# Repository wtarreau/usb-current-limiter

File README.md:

# Fixed or adjustable USB current limiter

When designing USB-powered devices, it's very important to be able to limit the current in order to protect the new device, as well as the USB port (typically the computer's). A simple serial resistor doesn't work as it causes a voltage drop that the device might not necessarily be able to cope with.

## Simple solution

It's easy to make a current limiter using a good old LM317, there are hundreds of such designs everywhere on the net. The main issue is that it drops at least 3 Volts, so you have to bring a 8V power supply on your USB connections, which can be even more dangerous for the board and the PC.

Instead, this project makes use of [Micrel's (now Microchip) MIC2544](http://ww1.microchip.com/downloads/en/DeviceDoc/mic2544.pdf). It's a high-side current limiter switch. It's perfect for hobbyists as it comes in an easily solderable SOP8 package and only requires one external resistor to set the current limit and an optional LED to report the overcurrent condition. The SOP8 package is large enough to let the two USB D+/D- lanes pass under, and allows to make an easy single-sided PCB. It can limit from something like 100mA to 1.5A or so.

The device photographed below was made the evening I found it in my mailbox. It was picked a bit too early from the acid bath, which explains why the copper tracks are not clean, but they are OK. At the last moment I preferred to solder a tiny 1k potentiometer that I already had instead of a fixed divider. The current limit precision is not very precise but we're speaking about saving chips from frying, so even 10% accuracy would be awesome.

Below it is connected to a freshly assembled [Breadbee board](https://github.com/breadbee/breadbee) board which it managed to protect:

## Schematic

The schematic was made with Eagle 7.7 and is provided in the directory.

## Board

The board is single-sided and doens't need any hole. A few versions of the rendered PCB are provided in the [output directory](output/), at 300 and 600 dpi and as a PDF. It's also provided as an Eagle `.brd` file.

## Bill of materials

Name | Value
-----|-------
 IC1 | MIC2544
 R1  | Rset = 230/current. e.g. 1k = 230mA
 R2  | 330-510 ohm (optional, for the overcurrent LED)
 R3  | optional, extra inrush current (230/Iamp)
 C1  | optional, inrush current duration. E.g. 1 µF
 D1  | optional, overcurrent red LED
 J1  | USB-A male connector (or PCB traces)
 X1  | USB-A female connector

## Other options

Other options include [ANALOGIC TECH's AAT4610](http://www1.futureelectronics.com/doc/ANALOGICTECH%20-%20AATI/AAT4610IGV-T1.pdf), which comes in a much smaller SOT23-5 package and doesn't have a LED output, or making your own solution using a shunt resistor and a rail-to-rail op amp such as [Microchip's MCP6001](https://ww1.microchip.com/downloads/en/DeviceDoc/MCP6001-1R-1U-2-4-1-MHz-Low-Power-Op-Amp-DS20001733L.pdf), coupled with a high-side, low-voltage, P-channel MOSFET. In the end, the MIC2544 already has everything included and is quite cheap so it seems to remain the best option for hobbyists.

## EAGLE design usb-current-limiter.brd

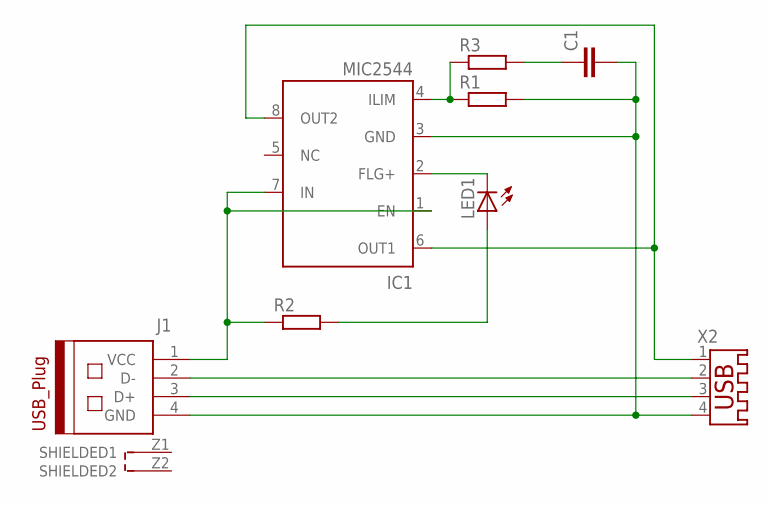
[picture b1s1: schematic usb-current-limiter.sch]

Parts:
C1: C-EUC0805K; C0805K
IC1: MIC2544; SO-08
J1: 629004113921
LED1: LEDCHIPLED_0805; CHIPLED_0805
R1, R2, R3: R-EU_M0805; M0805
X2: USB-A003

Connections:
unnamed: IC1.1 (EN), IC1.7 (IN), J1.1 (VCC), R2.1
unnamed: J1.2 (D-), X2.2
unnamed: J1.3 (D+), X2.3
unnamed: C1.2, IC1.3 (GND), J1.4 (GND), R1.2, X2.4
unnamed: IC1.6 (OUT1), IC1.8 (OUT2), X2.1
unnamed: IC1.4 (ILIM), R1.1, R3.1
unnamed: IC1.2 (FLG+), LED1.C
unnamed: LED1.A, R2.2
unnamed: C1.1, R3.2

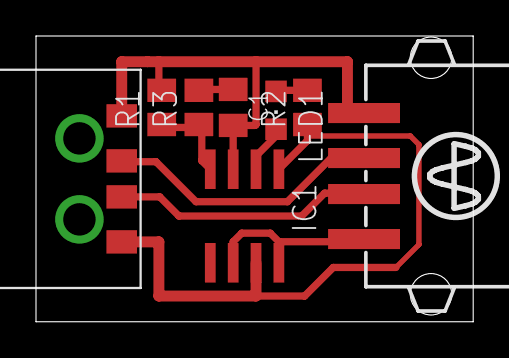
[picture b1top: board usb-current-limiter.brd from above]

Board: 2 copper layers, 24.3 x 15.9 mm, 8 parts (0 on the bottom side), 9 nets.

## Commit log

2020-09-07 First working version
    This one is easy to solder, uses 0805 resistors and an SOP8 package
    for the MIC2544. It uses no PTH components.
2020-09-07 output: provide PNG and PDF outputs
    This is the top side (both copper and components) in PDF and in PNG at
    300 and 600 DPI respectively, ready to be printed, and the schematic.
2020-09-07 photos: add a few photos
    People love photos!
2020-09-07 add a README

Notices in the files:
parts and their libraries:
Wurth_Elektronik_Electromechanic_Input-O: Copyright: Würth Elektronik
